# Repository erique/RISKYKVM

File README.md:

# RISKYKVM
Amiga adapter targets KVMs, but can be used as USB to DB9 and Amiga Keyabord interface

Project is based on following projects:
- Mist (USB HID parser stack)
- Mouse Driver - sq7bti.
- Simon Inns smallymouse2 mouse quadrature encoding
- Amiga Keyboard handler: https://github.com/gianlucarenzi/stalker
- WCH Example projects for CH32V203

## BOM
- "C1,C2,C3,C4,C5,C6" - 100nF 0603 
- "C9" - 0.1μF 0603
- "D1,D2" - LED 0805
- "F1" - Fuse 1206 500MA
- "J1" - DB9_Plug
- "J2" - Conn_01x02
- "J3" - USB_1
- "J4" - Conn_01x08
- "R1,R3" - aprox 200OHM (based on LED used)
- "R2" - 10K
- "U1" - CH32V203C8T6
- "U2" - LM1117MP-3.3 SOT-89

## Programming
WCH-LINK programmer is needed for initial programming of bootloader (bootloader.hex), then you can program application (RISKYKVM.UPD) using FAT32 formatted USB FLash drive.
To program bootloader or standard version of firmware use MounRiver IDE.

### Programming application firmware with custom bootloader.
1. Short CLK and DIO pins togeter, and power on device. When RDY LED starts to blink few times.
2. Insert USB Flash drive with RISKYKVM.UPD file in root directory.
3. If flashing is sucessful RDY LED will start slowly flashing 10x, if process failes then RDY flash either will be off, or will start flashing quickly 100x.
4. Power off device, remove jumper or disconnect CLK and DIO pins.
5. Device is ready to use.

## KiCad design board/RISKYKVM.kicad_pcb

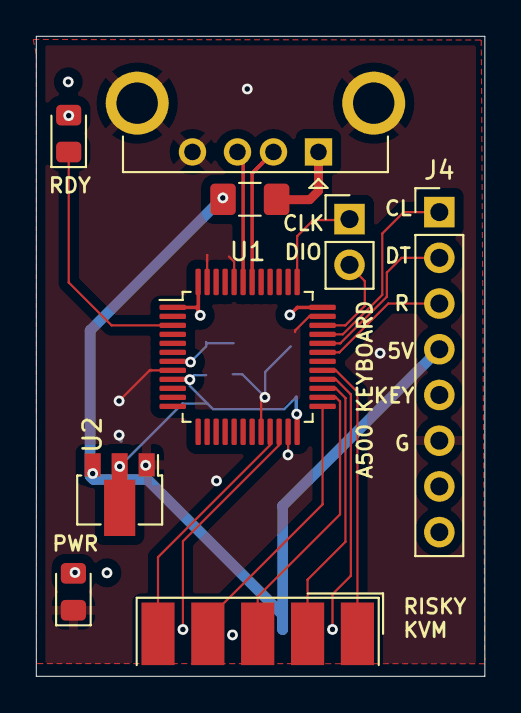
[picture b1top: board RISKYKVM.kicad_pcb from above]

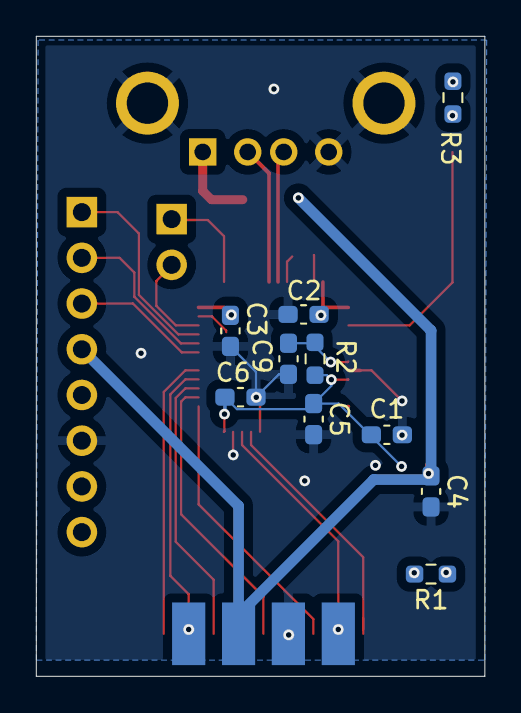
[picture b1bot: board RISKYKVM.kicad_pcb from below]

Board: 4 copper layers, 24.9 x 35.6 mm, 19 parts (10 on the bottom side), 22 nets.

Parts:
C1, C2, C3, C4, C5, C6: C; C_0603_1608Metric_Pad1.08x0.95mm_HandSolder
C9: 0.1μF; C_0603_1608Metric_Pad1.08x0.95mm_HandSolder
D1, D2: LED; LED_0805_2012Metric_Pad1.15x1.40mm_HandSolder
F1: Fuse; Fuse_1206_3216Metric_Pad1.42x1.75mm_HandSolder
J1: DE9_Plug; DSUB-9_Female_EdgeMount_P2.77mm
J2: Conn_01x02; PinHeader_1x02_P2.54mm_Vertical
J3: USB_1; USB_A_CONNFLY_DS1095-WNR0
J4: Conn_01x08; PinHeader_1x08_P2.54mm_Vertical
R1, R3: 2.2k; R_0603_1608Metric_Pad0.98x0.95mm_HandSolder
R2: R; R_0603_1608Metric_Pad0.98x0.95mm_HandSolder
U1: CH32V203C8T6; LQFP-48_7x7mm_P0.5mm
U2: LM1117MP-3.3; SOT-89-3

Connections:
+3.3V: C1.1, C2.1, C3.1, C5.1, C6.1, R1.2, R2.1, R3.2, U1.1 (VBAT), U1.9 (VDDA), U1.24 (VDD_VIO1), U1.36 (VDD_2), U1.48 (VDD_VIO_3), U2.2 (VO)
+5V: C4.1, F1.2, J1.7, J4.4, U2.3 (VI)
/KB_CLK: J4.1, U1.33 (PA12_USB1DP(FT))
/KB_DATA: J4.2, U1.32 (PA11_USB1DM(FT))
/KB_RESET: J4.3, U1.31 (PA10(FT))
/LED1: D2.1 (K), U1.3 (PC14_OSC32IN)
/NRST: C9.1, R2.2, U1.7 (NRST)
/PIN1: J1.1, U1.29 (PA8(FT))
/PIN2: J1.2, U1.27 (PB14(FT))
/PIN3: J1.3, U1.26 (PB13(FT))
/PIN4: J1.4, U1.25 (PB12(FT))
/PIN5: J1.5, U1.21 (PB10(FT))
/PIN6: J1.6, U1.28 (PB15(FT))
/PIN9: J1.9, U1.22 (PB11(FT))
/SWCLK: J2.1, U1.37 (PA14_SWCLK(FT))
/SWDIO: J2.2, U1.34 (PA13_SWDIO(FT))
/USB_DM: J3.2 (D-), U1.42 (PB6_USB2DM(FT))
/USB_DP: J3.3 (D+), U1.43 (PB7_USB2DP(FT))
GND: C1.2, C2.2, C3.2, C4.2, C5.2, C6.2, C9.2, D1.1 (K), J1.8, J3.4 (GND), J3.5 (Shield), J4.6, U1.8 (VSSA), U1.20 (PB2_BOOT1(FT)), U1.23 (VSS1), U1.35 (VSS_2), U1.44 (BOOT0), U1.47 (VSS_3), U2.1 (GND)
unnamed: D1.2 (A), R1.1
unnamed: D2.2 (A), R3.1
unnamed: F1.1, J3.1 (VBUS)

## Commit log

2024-08-09 v0.2
2024-08-11 Replace keybard library with my own one, some refactoring
2024-08-11 Project tidy up
2024-08-25 Fix issues related to BOOT0 and BOOT1
2024-08-25 KEY in Amiga Port missing
2024-08-28 Upgrade project to KiCad 8 Tidy up board projecy
2024-09-06 Adapt firmaware to latest PCB design
2024-09-07 Some bugfixes to fix mouse movements and scroll functionality
2024-09-08 Keybd mapping fixes
2024-09-21 Set up compiler with optimizations
2024-09-26 Custom bootloader Refactored project to allow use of custom bootloader
2024-09-28 Update README.md
    Add picture
2024-10-21 Reset and IRQ support
2024-10-27 tidy up
2024-11-23 reset fix, and watchdog, delete obj files
2024-11-23 update gitignore
2024-11-23 New keyboard combo for reset. Optimisations setup.
2024-12-28 add Dockerfile and Makefile
2024-12-29 Minimize docker image + use amd64
2024-12-29 .gitignore 'build' dir
